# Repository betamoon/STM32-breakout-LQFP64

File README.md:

# STM32-breakout-LQFP64

Does exactly what it says it does on the label.

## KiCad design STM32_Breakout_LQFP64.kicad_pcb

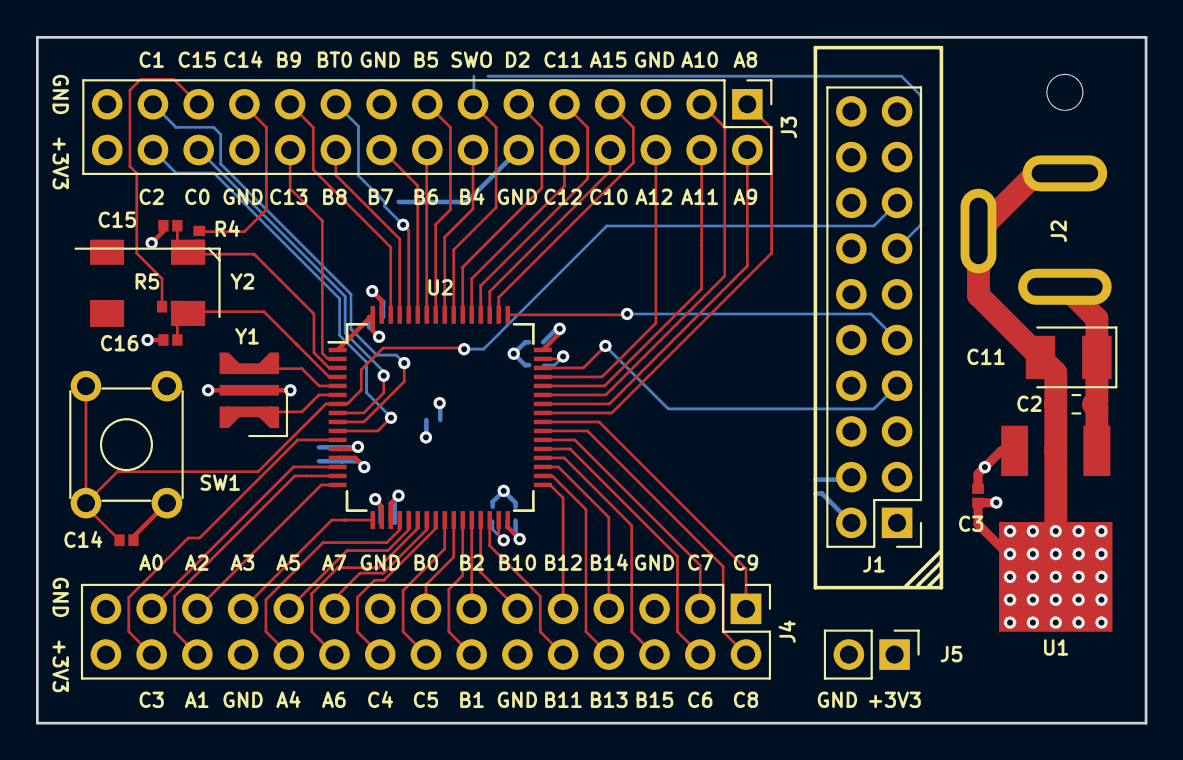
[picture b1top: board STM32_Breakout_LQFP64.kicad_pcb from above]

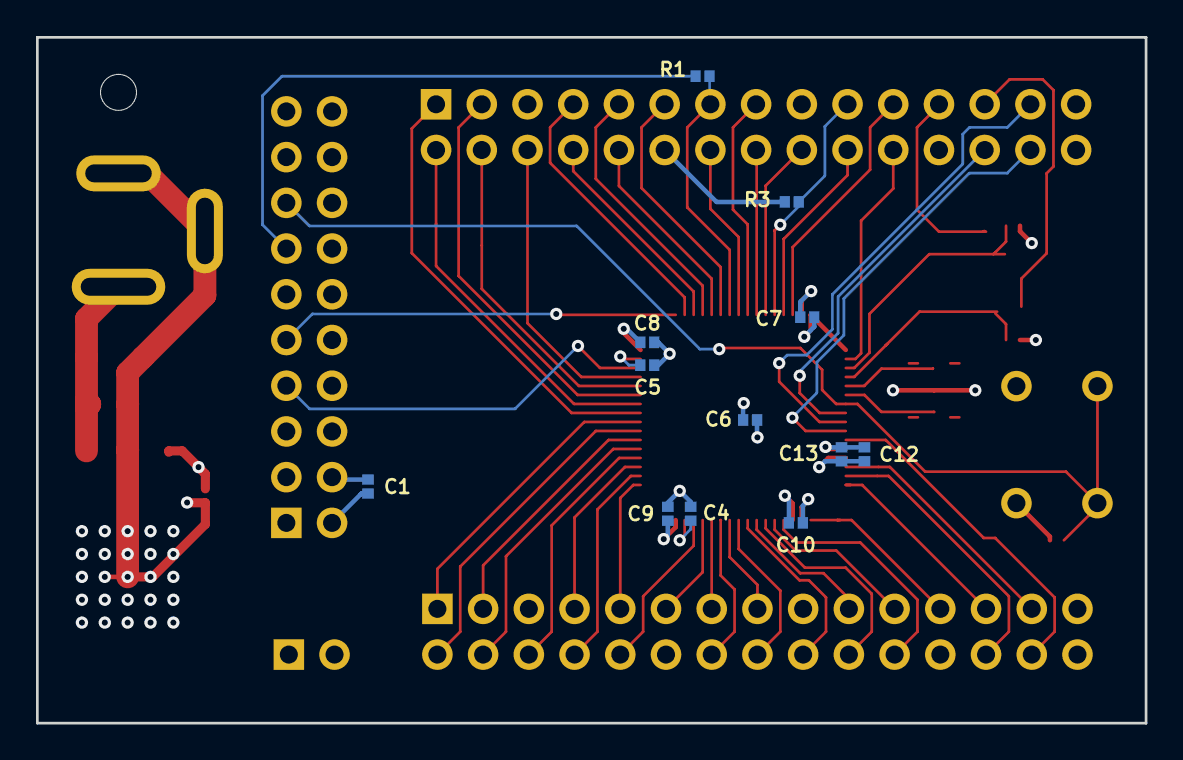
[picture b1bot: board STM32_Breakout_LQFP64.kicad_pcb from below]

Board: 4 copper layers, 61.6 x 38.1 mm, 31 parts (12 on the bottom side), 62 nets.

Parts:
C1, C3, C4, C5: 2.2uF; C_0402_1005Metric
C2: 100nF; C_0603_1608Metric_Pad0.84x1.00mm_HandSolder
C6: 4.7uF; C_0402_1005Metric
C7, C8, C9, C10, C13, C14, C15, C16: 100nF; C_0402_1005Metric
C11: 10uF; CP_EIA-3528-21_Kemet-B_Pad1.63x2.40mm_HandSolder
C12: 1uF; C_0402_1005Metric
J1: Conn_ARM_JTAG_SWD_20; PinHeader_2x10_P2.54mm_Vertical
J2: Barrel_Jack; DC_Power_Jack_CUI_PJ-057AH
J3, J4: Conn_02x14_Odd_Even; PinHeader_2x15_P2.54mm_Vertical
J5: Conn_01x02; PinHeader_1x02_P2.54mm_Vertical
NT1: Net-Tie_2; NetTie-2_SMD_Pad50mil
R1, R4, R5: 0; R_0402_1005Metric
R3: 10K; R_0402_1005Metric
SW1: SW_Push; SW_TH_Tactile_Omron_B3F-10xx
U1: KFxxBDT; TO-252
U2: STM32F205RxTx; LQFP-64_10x10mm_P0.5mm
Y1: Resonator; Resonator_SMD_muRata_CSTNE-3Pin_3.2x1.3mm_HandSoldering
Y2: ABS25-32.768KHZ-6-T; Crystal_SMD_Abracon_ABS25-4Pin_8.0x3.8mm

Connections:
+3V3: C1.1, C3.1, C6.1, C7.1, C8.1, C9.1, C10.1, C12.1, C13.1, J1.1, J1.2, J3.30, J4.30, J5.1, U1.3, U2.1, U2.13, U2.19, U2.32, U2.48, U2.64
+9V: C2.1, C11.1, J2.1, U1.1
BOOT0: J3.19, R3.1, U2.60
GND: C1.2, C3.2, C4.2, C5.2, C6.2, C7.2, C8.2, C9.2, C10.2, C12.2, C13.2, C14.2, C15.2, C16.2, J1.3, J1.4, J1.5, J1.6, J1.8, J1.10, J1.12, J1.14, J1.16, J1.18, J1.20, J3.5, J3.12, J3.17, J3.24, J3.29, J4.5, J4.12, J4.17, J4.24, J4.29, J5.2, NT1.2, R3.2, SW1.3, SW1.4, U1.2, U2.12, U2.18, U2.63, Y1.2
GNDPWR: C2.2, C11.2, J2.2, J2.3, NT1.1
unnamed: C4.1, U2.31
unnamed: C5.1, U2.47
unnamed: C15.1, R4.1, U2.3, Y2.1
unnamed: C16.1, R5.1, U2.4, Y2.4
unnamed: U2.5, Y1.3
unnamed: U2.6, Y1.1
PA0: J4.27, U2.14
PA1: J4.26, U2.15
PA2: J4.25, U2.16
PA3: J4.23, U2.17
PA4: J4.22, U2.20
PA5: J4.21, U2.21
PA6: J4.20, U2.22
PA7: J4.19, U2.23
PA8: J3.1, U2.41
PA9: J3.2, U2.42
PA10: J3.3, U2.43
PA11: J3.4, U2.44
PA12: J3.6, U2.45
PA15: J3.7, U2.50
PB0: J4.15, U2.26
PB1: J4.14, U2.27
PB2: J4.13, U2.28
PB3: J3.13, R1.2, U2.55
PB4: J3.14, U2.56
PB5: J3.15, U2.57
PB6: J3.16, U2.58
PB7: J3.18, U2.59
PB8: J3.20, U2.61
PB9: J3.21, U2.62
PB10: J4.11, U2.29
PB11: J4.10, U2.30
PB12: J4.9, U2.33
PB13: J4.8, U2.34
PB14: J4.7, U2.35
PB15: J4.6, U2.36
PC0: J3.26, U2.8
PC1: J3.27, U2.9
PC2: J3.28, U2.10
PC3: J4.28, U2.11
PC4: J4.18, U2.24
PC5: J4.16, U2.25
PC6: J4.4, U2.37
PC7: J4.3, U2.38
PC8: J4.2, U2.39
PC9: J4.1, U2.40
PC10: J3.8, U2.51
PC11: J3.9, U2.52
PC12: J3.10, U2.53
PC13: J3.22, U2.2
PC14: J3.23, R4.2
PC15: J3.25, R5.2
PD2: J3.11, U2.54
SWCLK: J1.9, U2.49
SWDIO: J1.7, U2.46
TRACESWO: J1.13, R1.1
~RST: C14.1, J1.15, SW1.1, SW1.2, U2.7

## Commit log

2019-06-30 Add .gitignore
2020-12-06 for safe keeping
2020-12-06 readme
